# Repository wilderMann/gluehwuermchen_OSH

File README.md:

# Glühwürmchen

### an opensource hardware project for youthwork and schools
Glühwürmchen is a small battery powerd PCB that is easy to solder for beginners and intended for the use in youthwork and schools.

You’ll find the english description below.

### Ein opensource hardware Projekt für Jugendarbeit und Schulen
Das Glühwürmchen ist eine kleine batteriebetriebene Schaltung die im Dunkeln leuchtet.
Es soll für Anfänger einfach zu löten sein und ist für den Einsatz in der Jugendarbeit gedacht.

### Wie komme ich an das Glühwürmchen?

Ihr müsst euch dieses Repository herunterladen, die Benötigten Bauteile einkaufen und die Platine produzieren lassen.
In der Regel zahlt es sich nicht aus nur ein Glühwürmchen produzieren zu lassen.
Ab etwa 100 Platinen macht die Bestellung Sinn.

Die Platine ist Beschriftet wo welches Bauteil hin soll. Die Lötpads sind extra groß um auch für Anfänger einfach lötbar zu sein.

#### Bauteilliste

Bezeichnung | Wert | Menge | Anmerkung | Links
 --- | --- | --- | --- | --- 
Metall-/Kohleschichtwiderstand|10...100kΩ|1|Je kleiner der Widerstand desto früher leuchtet die Schaltung|[Conrad](https://www.conrad.at/de/p/yageo-cfr-25jt-52-100k-kohleschicht-widerstand-100-k-axial-bedrahtet-0207-0-25-w-5-1-st-1417735.html) [DigiKey](https://www.digikey.at/de/products/detail/yageo/CFR-25JB-52-100K/245)
LED 5mm|Rot, Grün, Orange|1|Blau funktioniert mit kleinen Widerständen auch|[Conrad](https://www.conrad.at/de/p/barthelme-led-sortiment-gruen-rund-5-mm-120-mcd-35-20-ma-3-v-1666914.html) [DigiKey](https://www.digikey.at/de/products/detail/w%C3%BCrth-elektronik/151051RS11000/4490012)
Phototransistor|SFH300|1|Falls nicht verfügbar gehen auch andere "Standard" Phototransistoren|[Conrad](https://www.conrad.at/de/p/osram-fototransistor-5-mm-1130-nm-25-sfh-300-153805.html) [DigiKey](https://www.digikey.at/de/products/detail/ams-osram-usa-inc/SFH-300/2205884)
Batteriehalter|Für CR2032 Knopfzellen|1||[Conrad](https://www.conrad.at/de/p/tru-components-ch26-2032lf-knopfzellenhalter-1x-cr-2032-kontaktpole-1672595.html) [DigiKey](https://www.digikey.at/de/products/detail/mpd-memory-protection-devices/BS-3/275305)
Transistor|2N3904|1|am Besten eine Version mit aufgebogenen Füßchen|[Conrad](https://www.conrad.at/de/p/on-semiconductor-transistor-bjt-diskret-2n3904bu-to-92-3-anzahl-kanaele-1-npn-163350.html) [DigiKey](https://www.digikey.at/de/products/detail/onsemi/2N3904TAR/975250)
Knopfzelle|CR2032|1|andere CR20XX könnten auch in den Halter passen|[IKEA](https://www.ikea.com/at/de/p/plattboj-knopfzelle-80291156/)

#### Platine bestellen

Das Glühwürmchen könnt ihr euch bei diversen Herstellern produzieren lassen. Ein kostengünstiger Hersteller mit sitz in Europa ist [AISLER](https://aisler.net/).
Dort könnt ihr relativ einfach die **gluehwurmchen.kicad_pcb** Datei hochladen und bestellen.

# Glühwürmchen
### an opensource hardware project for youthwork and schools
Glühwürmchen is a small battery powerd PCB that is easy to solder for beginners and intended for the use in youthwork and schools.

### How do i get one?

You have to clone the repository, buy the components and order the PCB.
Usually its cheaper to order those in bigger quantities, starting with about 100 Glühwürmchen.

The PCB is marked, so its easy to assemble, also the pads are extra large to make soldering easier for beginners.

#### Bill of Materials

Name | Value | Amount | Comment | Links
 --- | --- | --- | --- | --- 
Resistor|10...100kΩ|1|for smaller values, the Gluhwurmchen will light up earlier|[DigiKey](https://www.digikey.co.uk/en/products/detail/yageo/CFR-25JB-52-100K/245)
LED 5mm|red, green, orange|1|blue might work with small resistor values|[DigiKey](https://www.digikey.co.uk/en/products/detail/w%C3%BCrth-elektronik/151051RS11000/4490012)
Phototransistor|SFH300|1|other "standard" phototransistors might also work|[DigiKey](https://www.digikey.co.uk/en/products/detail/ams-osram-usa-inc/SFH-300/2205884)
Battery holder|for CR2032 button cells|1||[DigiKey](https://www.digikey.co.uk/en/products/detail/mpd-memory-protection-devices/BS-3/275305)
Transistor|2N3904|1|get one with formed leads|[DigiKey](https://www.digikey.co.uk/en/products/detail/onsemi/2N3904TAR/975250)
Button cell|CR2032|1|other CR20XX might also fit into the holder|[IKEA](https://www.ikea.com/gb/en/p/plattboj-lithium-battery-80291156/)

#### Ordering the PCB

You can order the PCB with different companys. A cheap and european manufacturer is [AISLER](https://aisler.net/).
There you can upload **gluehwurmchen.kicad_pcb** and order it.

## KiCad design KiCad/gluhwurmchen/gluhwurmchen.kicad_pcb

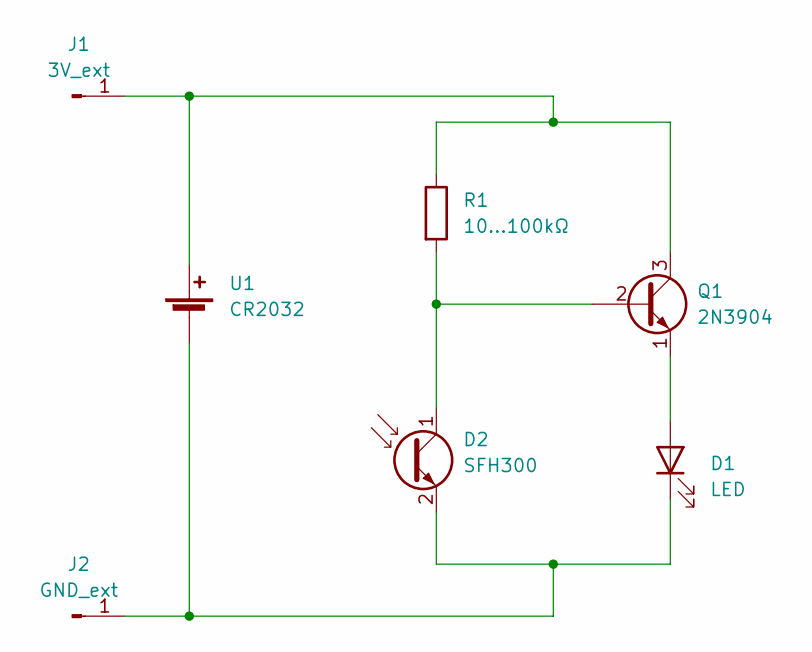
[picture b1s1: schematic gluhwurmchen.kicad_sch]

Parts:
D1: LED; LED_D5.0mm_handsolder
D2: SFH300; LED_D5.0mm_Clear_handsolder
J1: 3V_ext; SolderWirePad_1x01_SMD_2x2mm
J2: GND_ext; SolderWirePad_1x01_SMD_2x2mm
Q1: 2N3904; TO-92L_Inline_Handsolder
R1: 10...100kΩ; R_Axial_12.7mm_handsolder
U1: CR2032; CR2032_batteryholder

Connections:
unnamed: D1.2 (A), Q1.1 (E)
unnamed: D1.1 (K), D2.2 (E), J2.1, U1.2 (-)
unnamed: D2.1 (C), Q1.2 (B), R1.2
unnamed: J1.1, Q1.3 (C), R1.1, U1.1 (+)

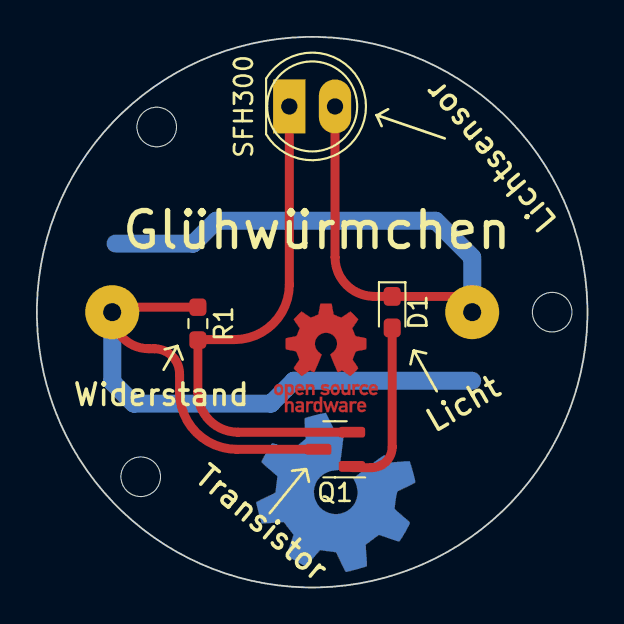
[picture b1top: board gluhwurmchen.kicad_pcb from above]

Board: 2 copper layers, 30.6 x 30.6 mm, 10 parts (1 on the bottom side), 4 nets.

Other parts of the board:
1, 2, 3: MountingHole_2.2mm_M2

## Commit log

2022-09-30 added images
2022-09-30 readme first draft
2022-09-30 repaired images
2022-09-30 images arrange
2022-09-30 fixed image
2022-09-30 images fixed again
2022-09-30 english translation
2022-09-30 adding english translation
2022-10-11 english translation, links updated, added pictures,bigger pads
2022-10-11 remove VScodium specific files
2022-10-11 added vscodium files
2022-10-11 finished translation, updated links, bigger pads
2022-10-11 added english pictures
2022-10-11 english pictures added
2022-10-11 added english pcb to main branch via a hirachical sheet
2022-10-11 fixed link
2023-02-14 changed trough-hole to smd
